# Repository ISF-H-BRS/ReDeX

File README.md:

# ReDeX: Water Purification Measurements

## Introduction

This repository contains a public archive of electronics, firmware and software developed as part of the project [ReDeX](https://www.h-brs.de/de/entwicklung-einer-reduktiven-behandlungsmethode-zur-entfernung-von-desinfektionsnebenprodukten-und) that was conducted at Bonn-Rhein-Sieg University of Applied Sciences from 2019 to 2022.

The goal of this sub-project was to develop a sensor network allowing various parameters inside a water purification system to be monitored and analyzed in order to gain a better understanding of the chemical and physical processes involved.

The system is composed of sensor nodes which can be used either as standalone devices connected to a PC over USB or as a sensor network accessed over TCP/IP via a central hub. Every sensor provides complete galvanic isolation in order to prevent any possibility of cross-currents which could potentially invalidate measurements.

The parameters that can be measured include conductance, pH/ORP levels and temperature. In addition a potentiostat for cyclic voltammetry was developed, providing a compliance voltage of ±4 V and a dynamic range of approx. 1 pA to 10 mA.

Every sensor node has a corresponding user software providing a GUI for individual measurements. The complete sensor network can be accessed via the central hub by means of a shared library with optional LabVIEW integration.

## License

All source code for the software and firmware components (including the LabVIEW code) is licensed under the terms of the GNU General Public License (GPL). All schematics and CAD files for EAGLE and FreeCAD are licensed under the terms of the Creative Commons Attribution-ShareAlike International Public License (CC BY-SA). See COPYING in the respective subdirectories for details.

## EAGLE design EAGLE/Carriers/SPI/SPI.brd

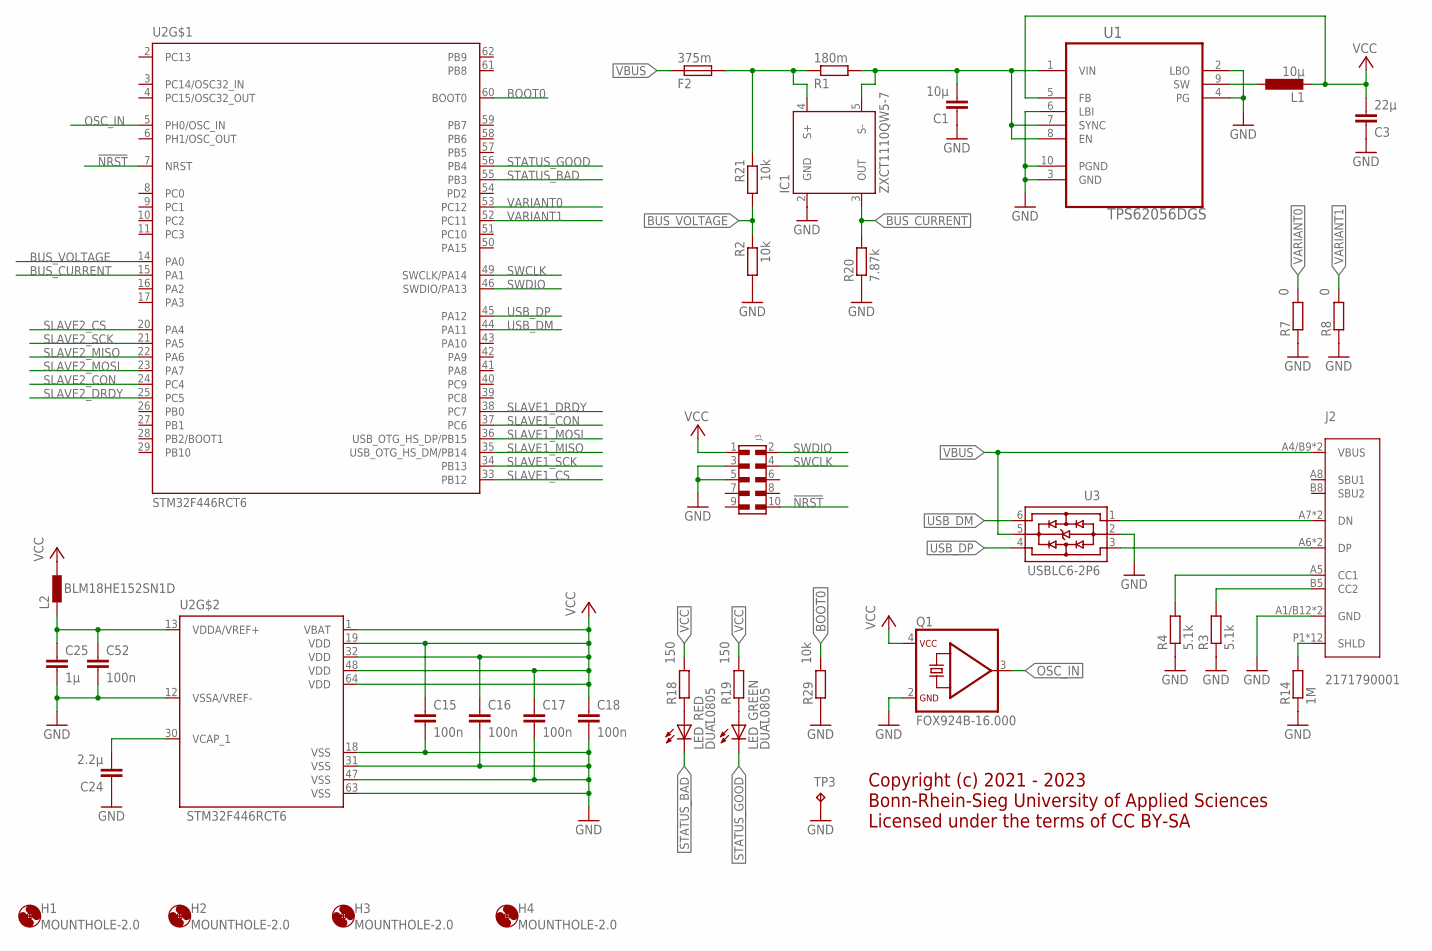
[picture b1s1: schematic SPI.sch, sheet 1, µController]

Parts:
C1: 10µ; C0603
C3: 22µ; C0603
C15, C16, C17, C18, C52: 100n; C0603
C24: 2.2µ; C0603
C25: 1µ; C0603
F2: 375m; R0603
H1, H2, H3, H4: MOUNTHOLE-2.0; 2.0
IC1: ZXCT1110QW5-7; SOT23-5L
J2: 2171790001; 2171790001_MOL
J3: 6210XX21021_62101021021; 62101021021
L1: 10µ; 2SMD
L2: BLM18HE152SN1D; 0603
LED_: DUAL0805; CHIPLEDX2
Q1: FOX924B-16.000; FOX924B
R1: 180m; R0603
R2, R21, R29: 10k; R0603
R3, R4: 5.1k; R0603
R7, R8: 0; R0603
R14: 1M; R0603
R18, R19: 150; R0603
R20: 7.87k; R0603
TP3: TP3.8X2.03; 3.8X2.03
U1: TPS62056DGS; SOP50P490X110-10N
U2: STM32F446RCT6; LQFP64
U3: USBLC6-2P6; SOT-666

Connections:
!NRST: J3.10, U2.7 (NRST)
BOOT0: R29.2, U2.60 (BOOT0)
BUS_CURRENT: IC1.3 (OUT), R20.2, U2.15 (PA1)
BUS_VOLTAGE: R2.1, R21.2, U2.14 (PA0)
GND: C1.1, C3.1, C15.2, C16.2, C17.2, C18.2, C24.1, C25.2, C52.2, IC1.2 (GND), J2.A1/B12 (GND), J2.B1/A12 (GND), J3.3, J3.5, Q1.2 (GND), R2.2, R3.1, R4.1, R7.1, R8.1, R14.1, R20.1, R29.1, TP3.TP, U1.2 (LBO), U1.3 (GND), U1.4 (PG), U1.6 (LBI), U1.10 (PGND), U2.12 (VSSA/VREF-), U2.18 (VSS), U2.31 (VSS), U2.47 (VSS), U2.63 (VSS), U3.2; also elsewhere on the board
unnamed: J2.P1 (SHLD), J2.P2 (SHLD), J2.P3 (SHLD), J2.P4 (SHLD), J2.S1 (SHLD), J2.S2 (SHLD), J2.S3 (SHLD), J2.S4 (SHLD), J2.S5 (SHLD), J2.S6 (SHLD), J2.S7 (SHLD), J2.S8 (SHLD), R14.2
unnamed: C1.2, IC1.5 (S-), R1.2, U1.1 (VIN), U1.7 (SYNC), U1.8 (EN)
unnamed: L1.P$1 (1), U1.9 (SW)
unnamed: J2.A6 (DP), J2.B6 (DP), U3.3
unnamed: J2.A7 (DN), J2.B7 (DN), U3.1
unnamed: J2.B5 (CC2), R3.2
unnamed: J2.A5 (CC1), R4.2
unnamed: C25.1, C52.1, L2.2, U2.13 (VDDA/VREF+)
unnamed: F2.2, IC1.4 (S+), R1.1, R21.1
unnamed: C24.2, U2.30 (VCAP_1)
unnamed: LED_.A1 (A), R18.1
unnamed: LED_.A2 (A), R19.1
OSC_IN: Q1.3 (OUT), U2.5 (PH0/OSC_IN)
SLAVE1_CON: U2.37 (PC6); also elsewhere on the board
SLAVE1_CS: U2.33 (PB12); also elsewhere on the board
SLAVE1_DRDY: U2.38 (PC7); also elsewhere on the board
SLAVE1_MISO: U2.35 (USB_OTG_HS_DM/PB14); also elsewhere on the board
SLAVE1_MOSI: U2.36 (USB_OTG_HS_DP/PB15); also elsewhere on the board
SLAVE1_SCK: U2.34 (PB13); also elsewhere on the board
SLAVE2_CON: U2.24 (PC4); also elsewhere on the board
SLAVE2_CS: U2.20 (PA4); also elsewhere on the board
SLAVE2_DRDY: U2.25 (PC5); also elsewhere on the board
SLAVE2_MISO: U2.22 (PA6); also elsewhere on the board
SLAVE2_MOSI: U2.23 (PA7); also elsewhere on the board
SLAVE2_SCK: U2.21 (PA5); also elsewhere on the board
STATUS_BAD: LED_.C1 (C), U2.55 (PB3)
STATUS_GOOD: LED_.C2 (C), U2.56 (PB4)
SWCLK: J3.4, U2.49 (SWCLK/PA14)
SWDIO: J3.2, U2.46 (SWDIO/PA13)
USB_DM: U2.44 (PA11), U3.6
USB_DP: U2.45 (PA12), U3.4
VARIANT0: R7.2, U2.53 (PC12)
VARIANT1: R8.2, U2.52 (PC11)
VBUS: F2.1, J2.A4/B9 (VBUS), J2.B4/A9 (VBUS), U3.5
VCC: C3.2, C15.1, C16.1, C17.1, C18.1, J3.1, L1.P$2 (2), L2.1, Q1.4 (VCC), R18.2, R19.2, U1.5 (FB), U2.1 (VBAT), U2.19 (VDD), U2.32 (VDD), U2.48 (VDD), U2.64 (VDD); also elsewhere on the board

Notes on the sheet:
Copyright (c) 2021 - 2023 Bonn-Rhein-Sieg University of Applied Sciences Licensed under the terms of CC BY-SA

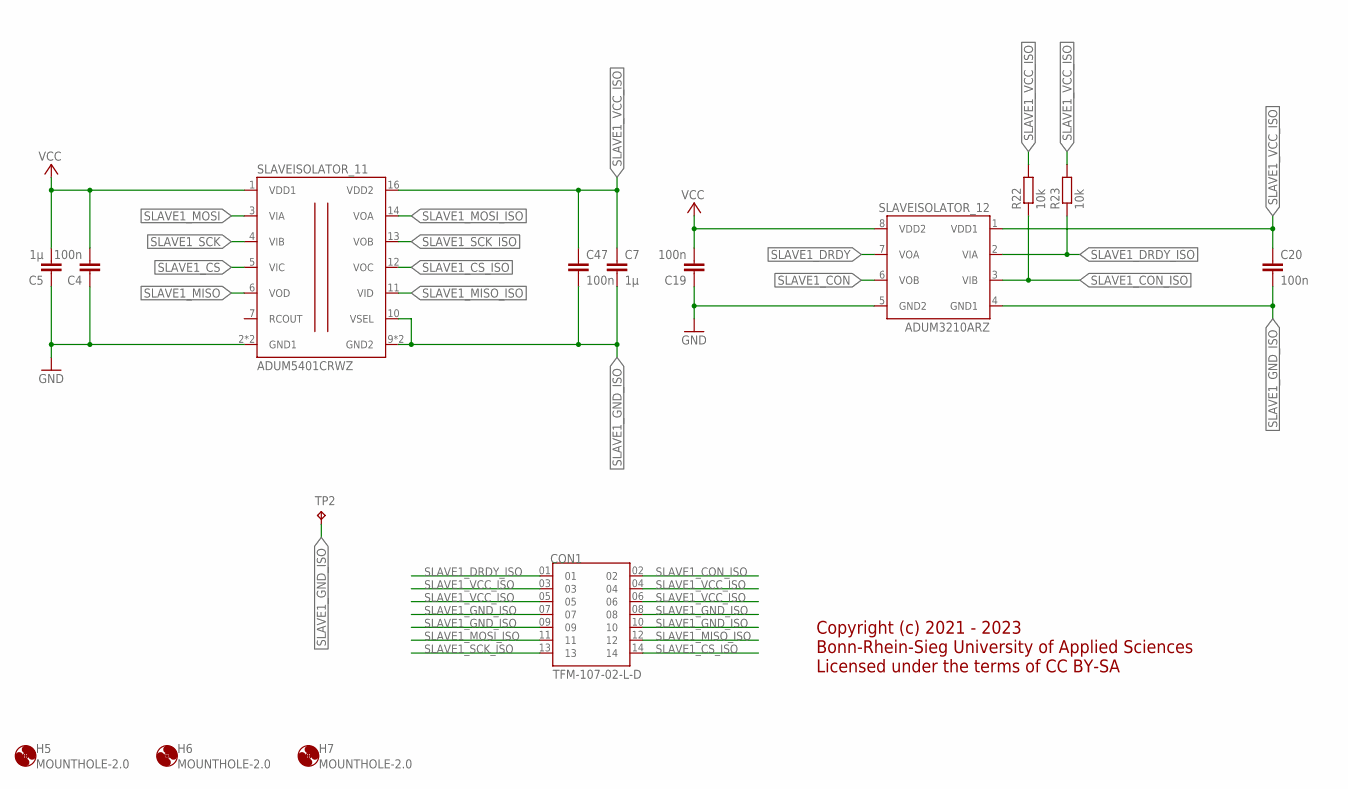
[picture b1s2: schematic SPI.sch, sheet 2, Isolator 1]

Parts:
C4, C19, C20, C47: 100n; C0603
C5, C7: 1µ; C0603
CON1: TFM-107-02-L-D; SAMTEC_TFM-107-02-L-D
H5, H6, H7: MOUNTHOLE-2.0; 2.0
R22, R23: 10k; R0603
SLAVEISOLATOR_11: ADUM5401CRWZ; SO16W
SLAVEISOLATOR_12: ADUM3210ARZ; SOIC8
TP2: TP3.8X2.03; 3.8X2.03

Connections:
GND: C4.1, C5.1, C19.1, SLAVEISOLATOR_11.2 (GND1), SLAVEISOLATOR_11.8 (GND1), SLAVEISOLATOR_12.5 (GND2); also elsewhere on the board
SLAVE1_CON: SLAVEISOLATOR_12.6 (VOB); also elsewhere on the board
SLAVE1_CON_ISO: CON1.02, R22.1, SLAVEISOLATOR_12.3 (VIB)
SLAVE1_CS: SLAVEISOLATOR_11.5 (VIC); also elsewhere on the board
SLAVE1_CS_ISO: CON1.14, SLAVEISOLATOR_11.12 (VOC)
SLAVE1_DRDY: SLAVEISOLATOR_12.7 (VOA); also elsewhere on the board
SLAVE1_DRDY_ISO: CON1.01, R23.1, SLAVEISOLATOR_12.2 (VIA)
SLAVE1_GND_ISO: C7.2, C20.2, C47.2, CON1.07, CON1.08, CON1.09, CON1.10, SLAVEISOLATOR_11.9 (GND2), SLAVEISOLATOR_11.10 (VSEL), SLAVEISOLATOR_11.15 (GND2), SLAVEISOLATOR_12.4 (GND1), TP2.TP
SLAVE1_MISO: SLAVEISOLATOR_11.6 (VOD); also elsewhere on the board
SLAVE1_MISO_ISO: CON1.12, SLAVEISOLATOR_11.11 (VID)
SLAVE1_MOSI: SLAVEISOLATOR_11.3 (VIA); also elsewhere on the board
SLAVE1_MOSI_ISO: CON1.11, SLAVEISOLATOR_11.14 (VOA)
SLAVE1_SCK: SLAVEISOLATOR_11.4 (VIB); also elsewhere on the board
SLAVE1_SCK_ISO: CON1.13, SLAVEISOLATOR_11.13 (VOB)
SLAVE1_VCC_ISO: C7.1, C20.1, C47.1, CON1.03, CON1.04, CON1.05, CON1.06, R22.2, R23.2, SLAVEISOLATOR_11.16 (VDD2), SLAVEISOLATOR_12.1 (VDD1)
VCC: C4.2, C5.2, C19.2, SLAVEISOLATOR_11.1 (VDD1), SLAVEISOLATOR_12.8 (VDD2); also elsewhere on the board

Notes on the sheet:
Copyright (c) 2021 - 2023 Bonn-Rhein-Sieg University of Applied Sciences Licensed under the terms of CC BY-SA

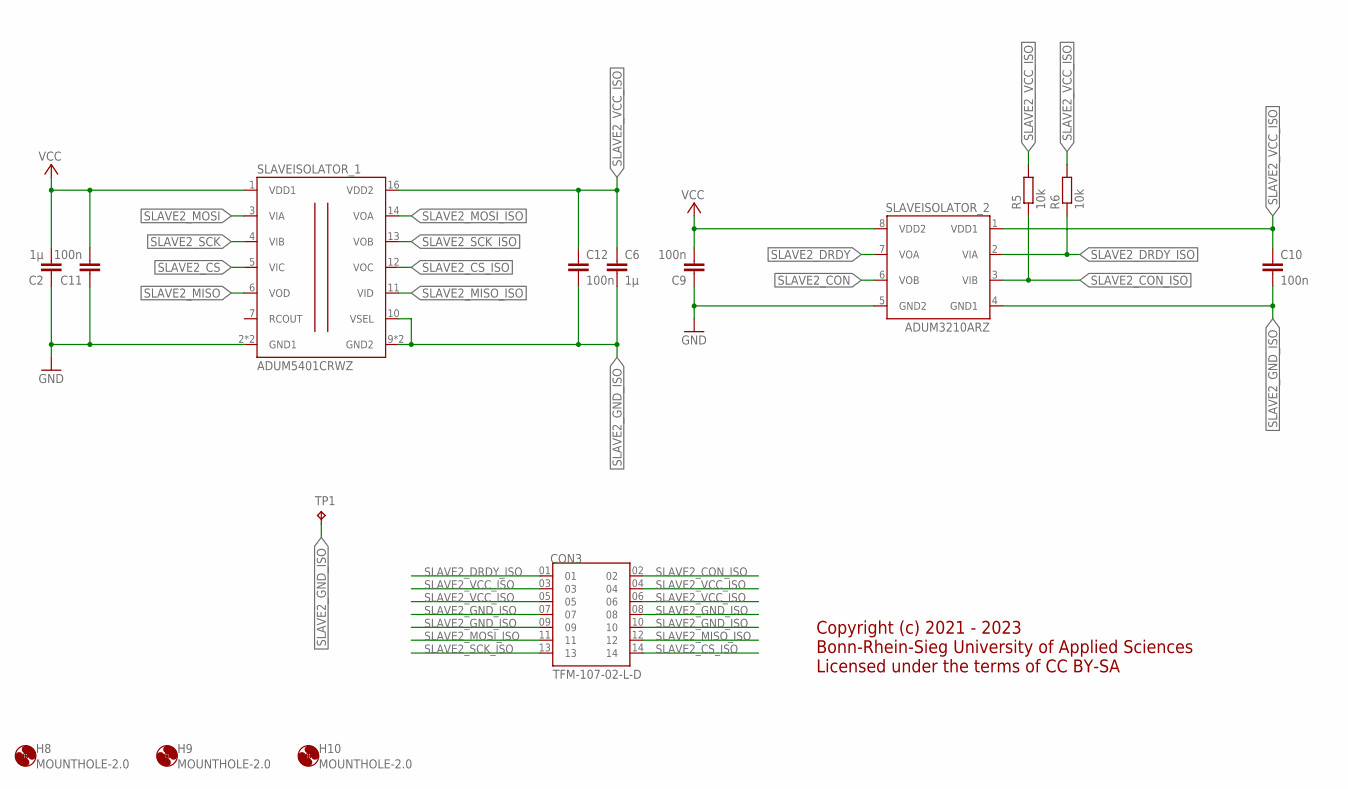
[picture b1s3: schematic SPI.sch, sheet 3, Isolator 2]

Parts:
C2, C6: 1µ; C0603
C9, C10, C11, C12: 100n; C0603
CON3: TFM-107-02-L-D; SAMTEC_TFM-107-02-L-D
H8, H9, H10: MOUNTHOLE-2.0; 2.0
R5, R6: 10k; R0603
SLAVEISOLATOR_1: ADUM5401CRWZ; SO16W
SLAVEISOLATOR_2: ADUM3210ARZ; SOIC8
TP1: TP3.8X2.03; 3.8X2.03

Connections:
GND: C2.1, C9.1, C11.1, SLAVEISOLATOR_1.2 (GND1), SLAVEISOLATOR_1.8 (GND1), SLAVEISOLATOR_2.5 (GND2); also elsewhere on the board
SLAVE2_CON: SLAVEISOLATOR_2.6 (VOB); also elsewhere on the board
SLAVE2_CON_ISO: CON3.02, R5.1, SLAVEISOLATOR_2.3 (VIB)
SLAVE2_CS: SLAVEISOLATOR_1.5 (VIC); also elsewhere on the board
SLAVE2_CS_ISO: CON3.14, SLAVEISOLATOR_1.12 (VOC)
SLAVE2_DRDY: SLAVEISOLATOR_2.7 (VOA); also elsewhere on the board
SLAVE2_DRDY_ISO: CON3.01, R6.1, SLAVEISOLATOR_2.2 (VIA)
SLAVE2_GND_ISO: C6.2, C10.2, C12.2, CON3.07, CON3.08, CON3.09, CON3.10, SLAVEISOLATOR_1.9 (GND2), SLAVEISOLATOR_1.10 (VSEL), SLAVEISOLATOR_1.15 (GND2), SLAVEISOLATOR_2.4 (GND1), TP1.TP
SLAVE2_MISO: SLAVEISOLATOR_1.6 (VOD); also elsewhere on the board
SLAVE2_MISO_ISO: CON3.12, SLAVEISOLATOR_1.11 (VID)
SLAVE2_MOSI: SLAVEISOLATOR_1.3 (VIA); also elsewhere on the board
SLAVE2_MOSI_ISO: CON3.11, SLAVEISOLATOR_1.14 (VOA)
SLAVE2_SCK: SLAVEISOLATOR_1.4 (VIB); also elsewhere on the board
SLAVE2_SCK_ISO: CON3.13, SLAVEISOLATOR_1.13 (VOB)
SLAVE2_VCC_ISO: C6.1, C10.1, C12.1, CON3.03, CON3.04, CON3.05, CON3.06, R5.2, R6.2, SLAVEISOLATOR_1.16 (VDD2), SLAVEISOLATOR_2.1 (VDD1)
VCC: C2.2, C9.2, C11.2, SLAVEISOLATOR_1.1 (VDD1), SLAVEISOLATOR_2.8 (VDD2); also elsewhere on the board

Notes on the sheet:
Copyright (c) 2021 - 2023 Bonn-Rhein-Sieg University of Applied Sciences Licensed under the terms of CC BY-SA

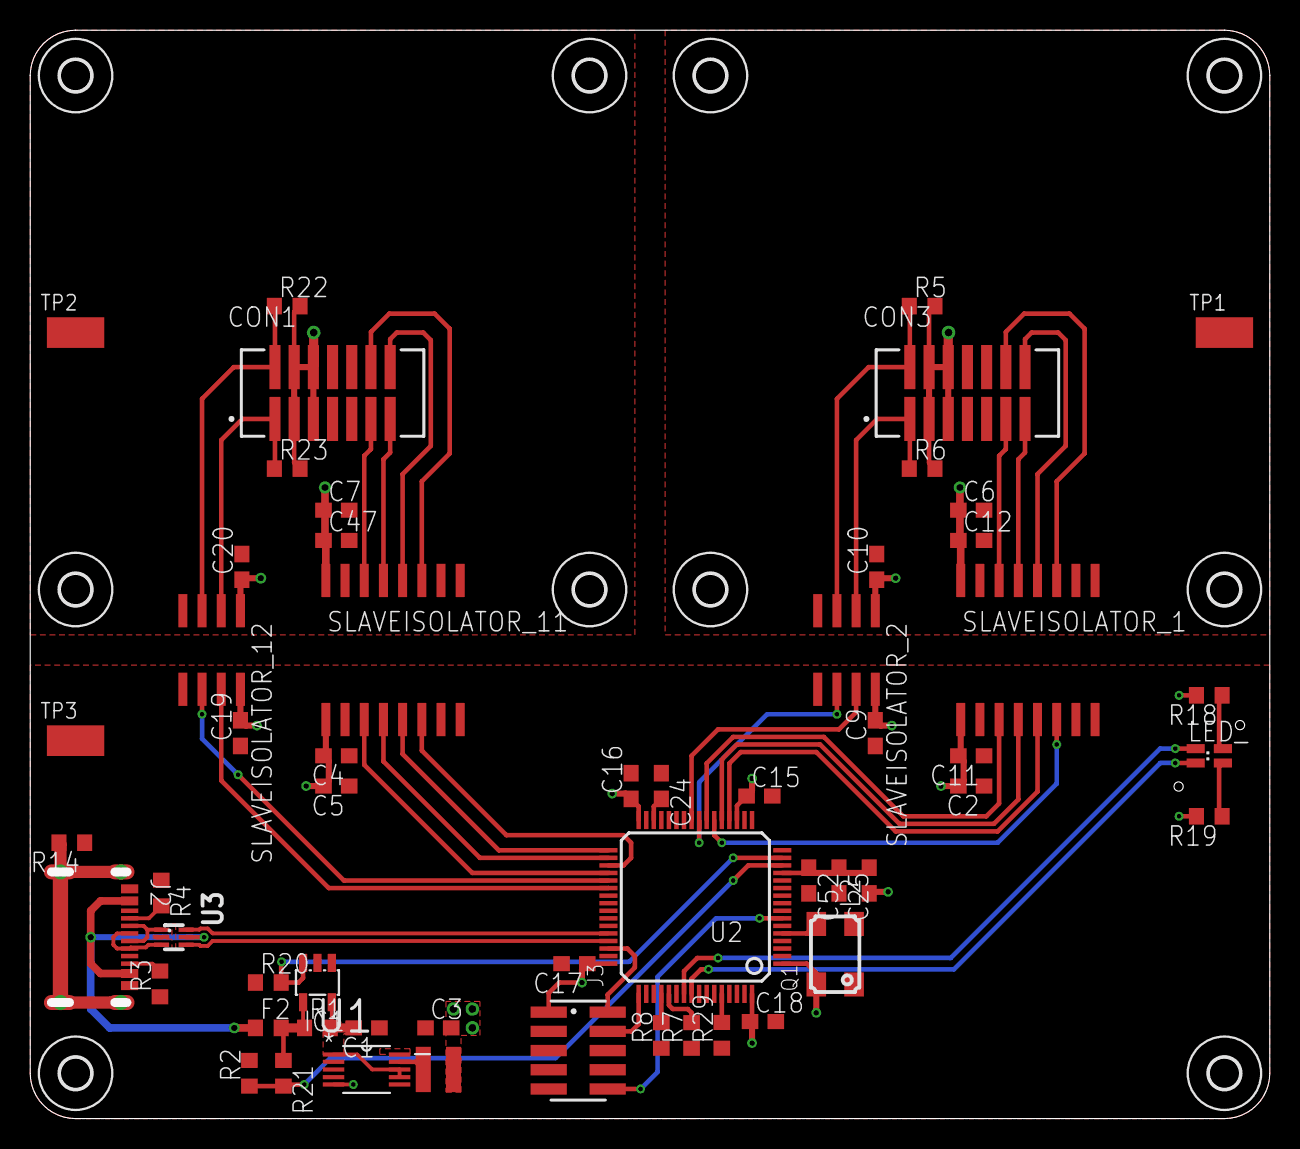
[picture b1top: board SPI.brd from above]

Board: 2 copper layers, 81.4 x 71.4 mm, 67 parts (0 on the bottom side), 56 nets.

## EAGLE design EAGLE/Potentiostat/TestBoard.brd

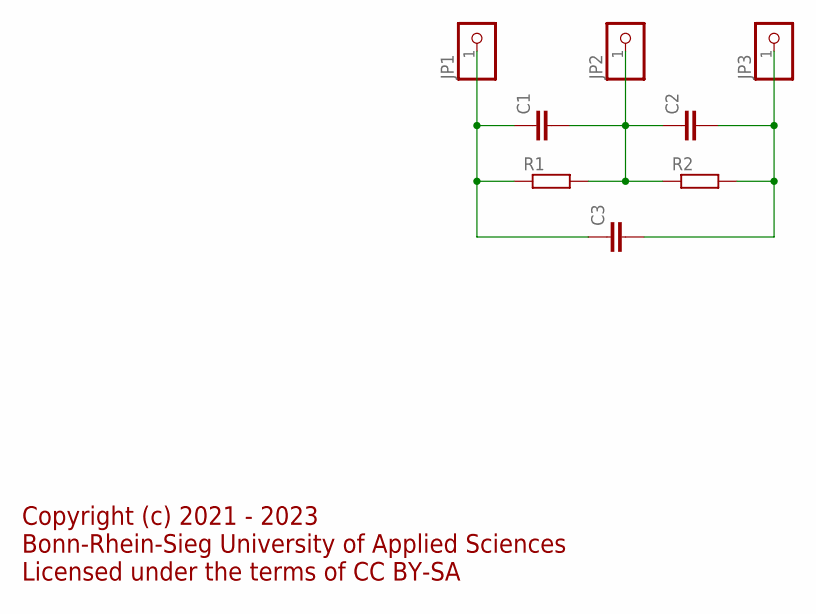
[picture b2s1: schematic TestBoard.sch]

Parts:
C1, C2, C3: C-EUC0603; C0603
JP1, JP2, JP3: PINHD-1X1; 1X01
R1, R2: R-EU_R0603; R0603

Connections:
unnamed: C1.1, C3.1, JP1.1, R1.1
unnamed: C1.2, C2.1, JP2.1, R1.2, R2.1
unnamed: C2.2, C3.2, JP3.1, R2.2

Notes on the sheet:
Copyright (c) 2021 - 2023 Bonn-Rhein-Sieg University of Applied Sciences Licensed under the terms of CC BY-SA

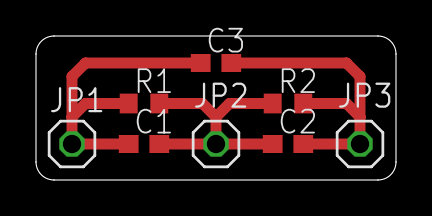
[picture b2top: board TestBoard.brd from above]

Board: 2 copper layers, 20.0 x 8.0 mm, 8 parts (0 on the bottom side), 3 nets.

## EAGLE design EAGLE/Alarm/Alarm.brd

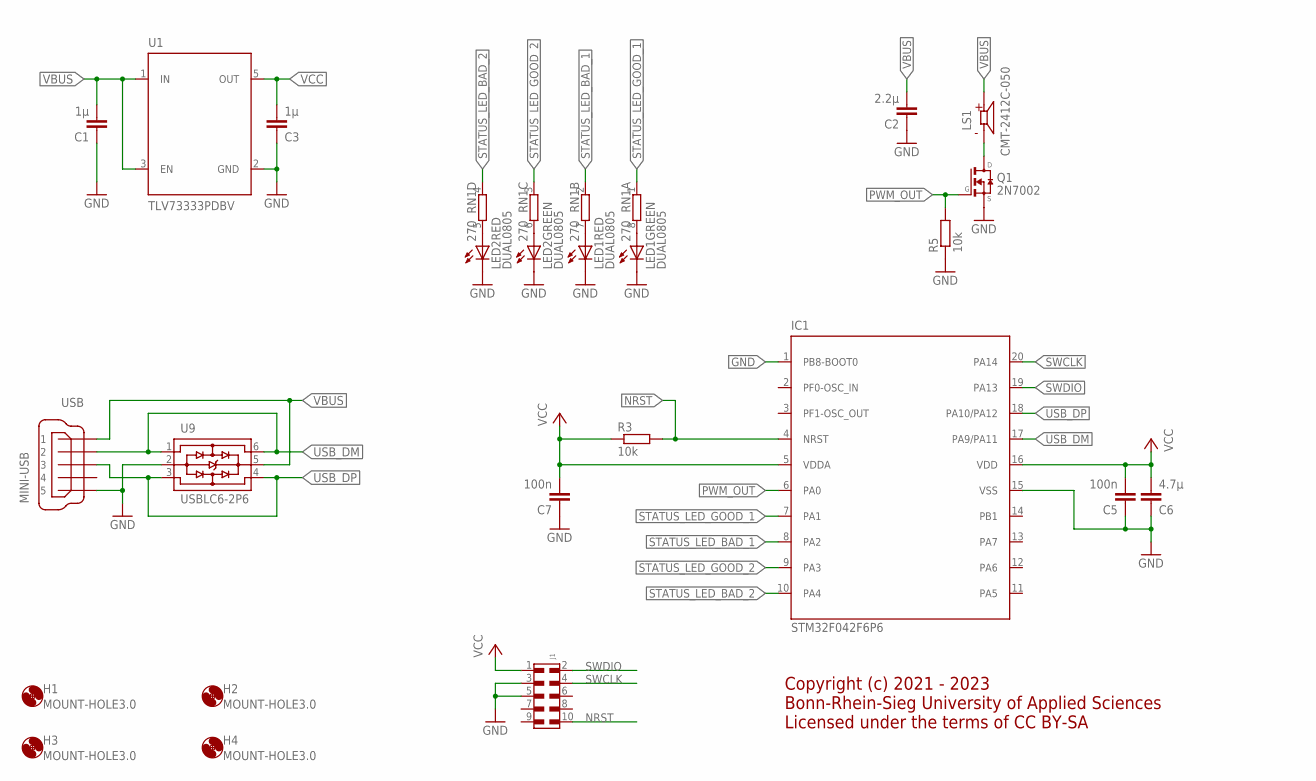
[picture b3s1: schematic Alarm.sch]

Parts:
C1, C3: 1µ; C0603
C2: 2.2µ; C0603
C5, C7: 100n; C0603
C6: 4.7µ; C0603
H1, H2, H3, H4: MOUNT-HOLE3.0; 3,0
IC1: STM32F042F6P6; TSSOP20
J1: 6210XX21021_62101021021; 62101021021
LED1, LED2: DUAL0805; CHIPLEDX2
LS1: CMT-2412C-050; CUI_CMT-2412C-050
Q1: 2N7002; SOT23
R3, R5: 10k; R0603
RN1: 270; EXB38V
U1: TLV73333PDBV; SOT-23
U9: USBLC6-2P6; SOT-666; PARTNO *
USB: MINI-USB; 32005-201

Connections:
GND: C1.1, C2.1, C3.1, C5.1, C6.1, C7.1, IC1.1 (PB8-BOOT0), IC1.15 (VSS), J1.3, J1.5, LED1.C1 (C), LED1.C2 (C), LED2.C1 (C), LED2.C2 (C), Q1.2 (S), R5.1, U1.2 (GND), U9.2, USB.5
unnamed: LED2.A1 (A), RN1.5 (2)
unnamed: LED2.A2 (A), RN1.6 (2)
unnamed: LED1.A1 (A), RN1.7 (2)
unnamed: LED1.A2 (A), RN1.8 (2)
unnamed: LS1.N, Q1.3 (D)
NRST: IC1.4 (NRST), J1.10, R3.2
PWM_OUT: IC1.6 (PA0), Q1.1 (G), R5.2
STATUS_LED_BAD_1: IC1.8 (PA2), RN1.2 (1)
STATUS_LED_BAD_2: IC1.10 (PA4), RN1.4 (1)
STATUS_LED_GOOD_1: IC1.7 (PA1), RN1.1
STATUS_LED_GOOD_2: IC1.9 (PA3), RN1.3 (1)
SWCLK: IC1.20 (PA14), J1.4
SWDIO: IC1.19 (PA13), J1.2
USB_DM: IC1.17 (PA9/PA11), U9.1, U9.6, USB.2
USB_DP: IC1.18 (PA10/PA12), U9.3, U9.4, USB.3
VBUS: C1.2, C2.2, LS1.P, U1.1 (IN), U1.3 (EN), U9.5, USB.1
VCC: C3.2, C5.2, C6.2, C7.2, IC1.5 (VDDA), IC1.16 (VDD), J1.1, R3.1, U1.5 (OUT)

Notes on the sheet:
Copyright (c) 2021 - 2023 Bonn-Rhein-Sieg University of Applied Sciences Licensed under the terms of CC BY-SA

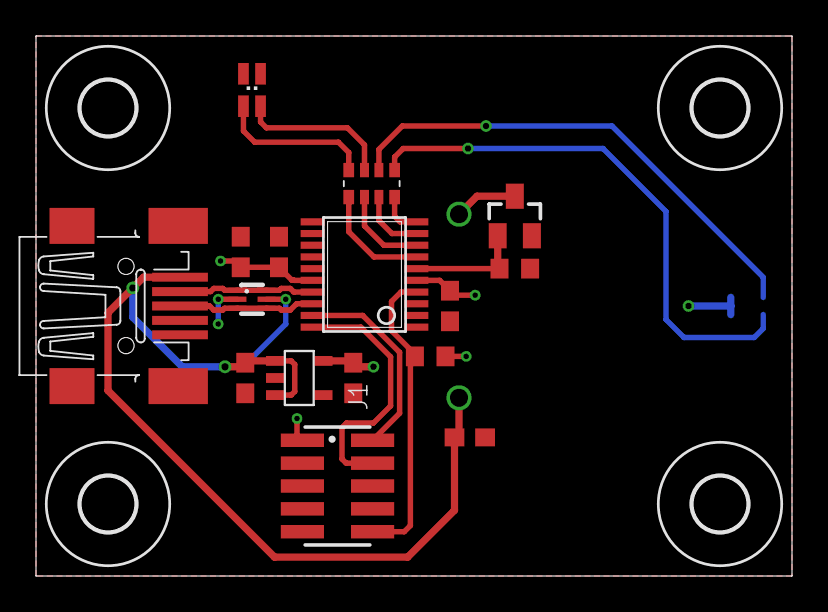
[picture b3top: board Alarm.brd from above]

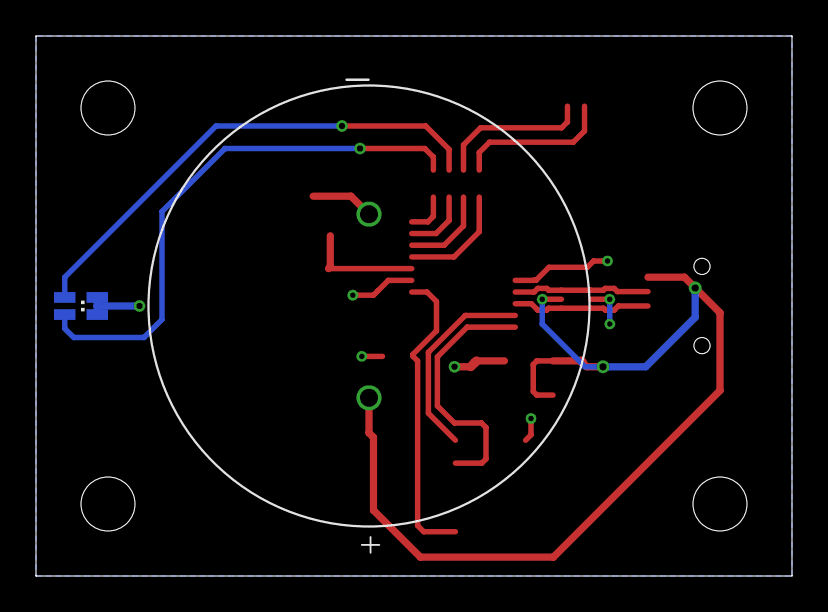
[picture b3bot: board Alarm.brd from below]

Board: 2 copper layers, 42.0 x 30.0 mm, 22 parts (2 on the bottom side), 18 nets.

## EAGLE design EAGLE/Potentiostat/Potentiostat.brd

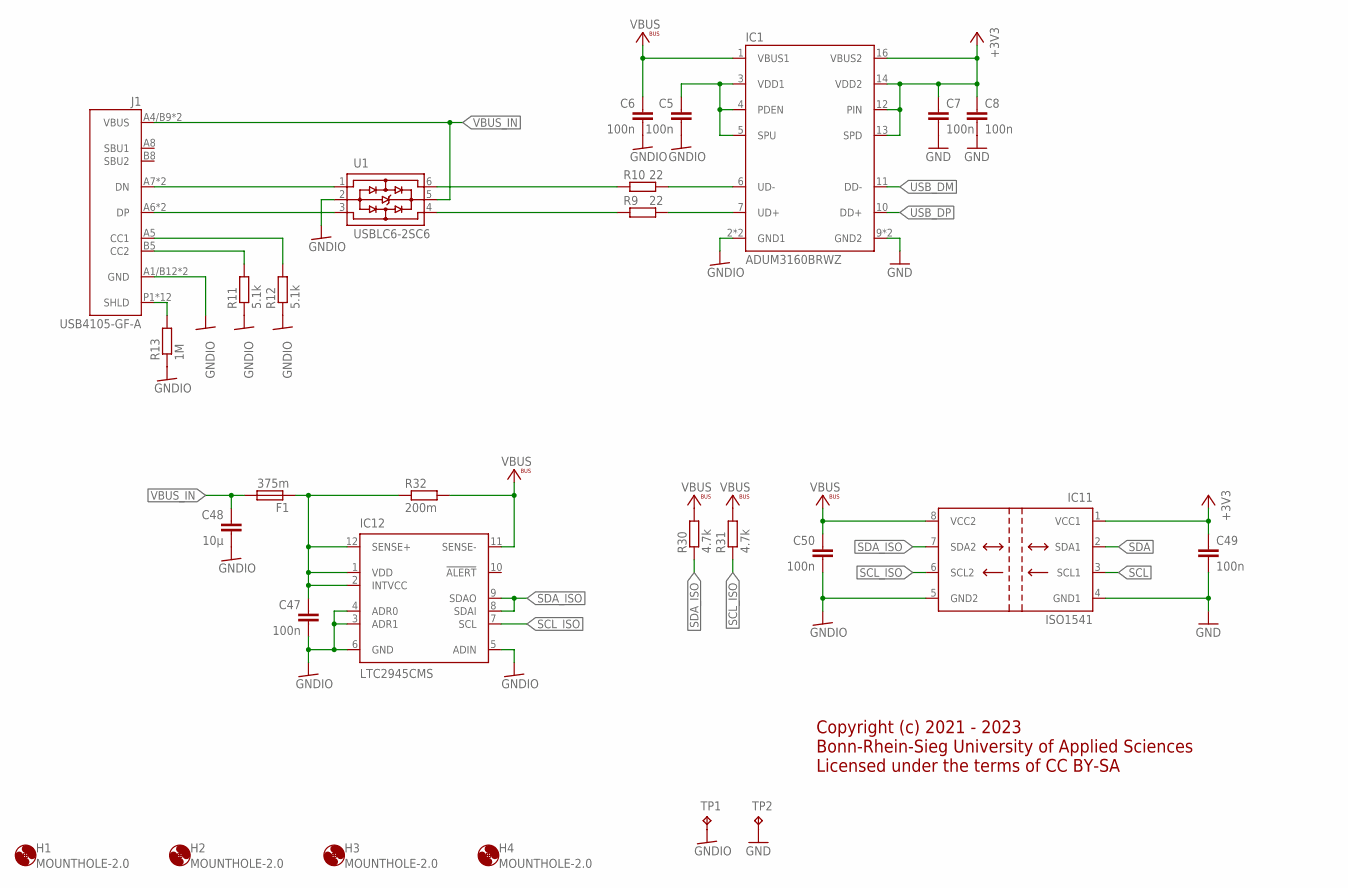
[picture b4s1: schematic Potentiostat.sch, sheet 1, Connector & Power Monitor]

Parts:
C5, C6, C7, C8, C47, C49, C50: 100n; C0603
C48: 10µ; C0603
F1: 375m; R0603
H1, H2, H3, H4: MOUNTHOLE-2.0; 2.0
IC1: ADUM3160BRWZ; SO16W
IC11: ISO1541; SOIC8
IC12: LTC2945CMS; MSOP12
J1: USB4105-GF-A
R9, R10: 22; R0603
R11, R12: 5.1k; R0603
R13: 1M; R0603
R30, R31: 4.7k; R0603
R32: 200m; R0805
TP1, TP2: TP3.8X2.03; 3.8X2.03
U1: USBLC6-2SC6; SOT23-6L

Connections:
+3V3: C7.1, C8.1, C49.1, IC1.12 (PIN), IC1.13 (SPD), IC1.14 (VDD2), IC1.16 (VBUS2), IC11.1 (VCC1); also elsewhere on the board
GND: C7.2, C8.2, C49.2, IC1.9 (GND2), IC1.15 (GND2), IC11.4 (GND1), TP2.TP; also elsewhere on the board
GNDIO: C5.2, C6.2, C47.2, C48.2, C50.2, IC1.2 (GND1), IC1.8 (GND1), IC11.5 (GND2), IC12.3 (ADR1), IC12.4 (ADR0), IC12.5 (ADIN), IC12.6 (GND), J1.A1/B12 (GND), J1.B1/A12 (GND), R11.1, R12.1, R13.1, TP1.TP, U1.2; also elsewhere on the board
unnamed: C5.1, IC1.3 (VDD1), IC1.4 (PDEN), IC1.5 (SPU)
unnamed: R10.1, U1.6
unnamed: R9.1, U1.4
unnamed: IC1.7 (UD+), R9.2
unnamed: C47.1, F1.1, IC12.1 (VDD), IC12.2 (INTVCC), IC12.12 (SENSE+), R32.1
unnamed: J1.A7 (DN), J1.B7 (DN), U1.1
unnamed: J1.A6 (DP), J1.B6 (DP), U1.3
unnamed: J1.A5 (CC1), R12.2
unnamed: J1.B5 (CC2), R11.2
unnamed: J1.P1 (SHLD), J1.P2 (SHLD), J1.P3 (SHLD), J1.P4 (SHLD), J1.S1 (SHLD), J1.S2 (SHLD), J1.S3 (SHLD), J1.S4 (SHLD), J1.S5 (SHLD), J1.S6 (SHLD), J1.S7 (SHLD), J1.S8 (SHLD), R13.2
unnamed: IC1.6 (UD-), R10.2
SCL: IC11.3 (SCL1); also elsewhere on the board
SCL_ISO: IC11.6 (SCL2), IC12.7 (SCL), R31.1
SDA: IC11.2 (SDA1); also elsewhere on the board
SDA_ISO: IC11.7 (SDA2), IC12.8 (SDAI), IC12.9 (SDAO), R30.1
USB_DM: IC1.11 (DD-); also elsewhere on the board
USB_DP: IC1.10 (DD+); also elsewhere on the board
VBUS: C6.1, C50.1, IC1.1 (VBUS1), IC11.8 (VCC2), IC12.11 (SENSE-), R30.2, R31.2, R32.2; also elsewhere on the board
VBUS_IN: C48.1, F1.2, J1.A4/B9 (VBUS), J1.B4/A9 (VBUS), U1.5

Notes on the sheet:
Copyright (c) 2021 - 2023 Bonn-Rhein-Sieg University of Applied Sciences Licensed under the terms of CC BY-SA

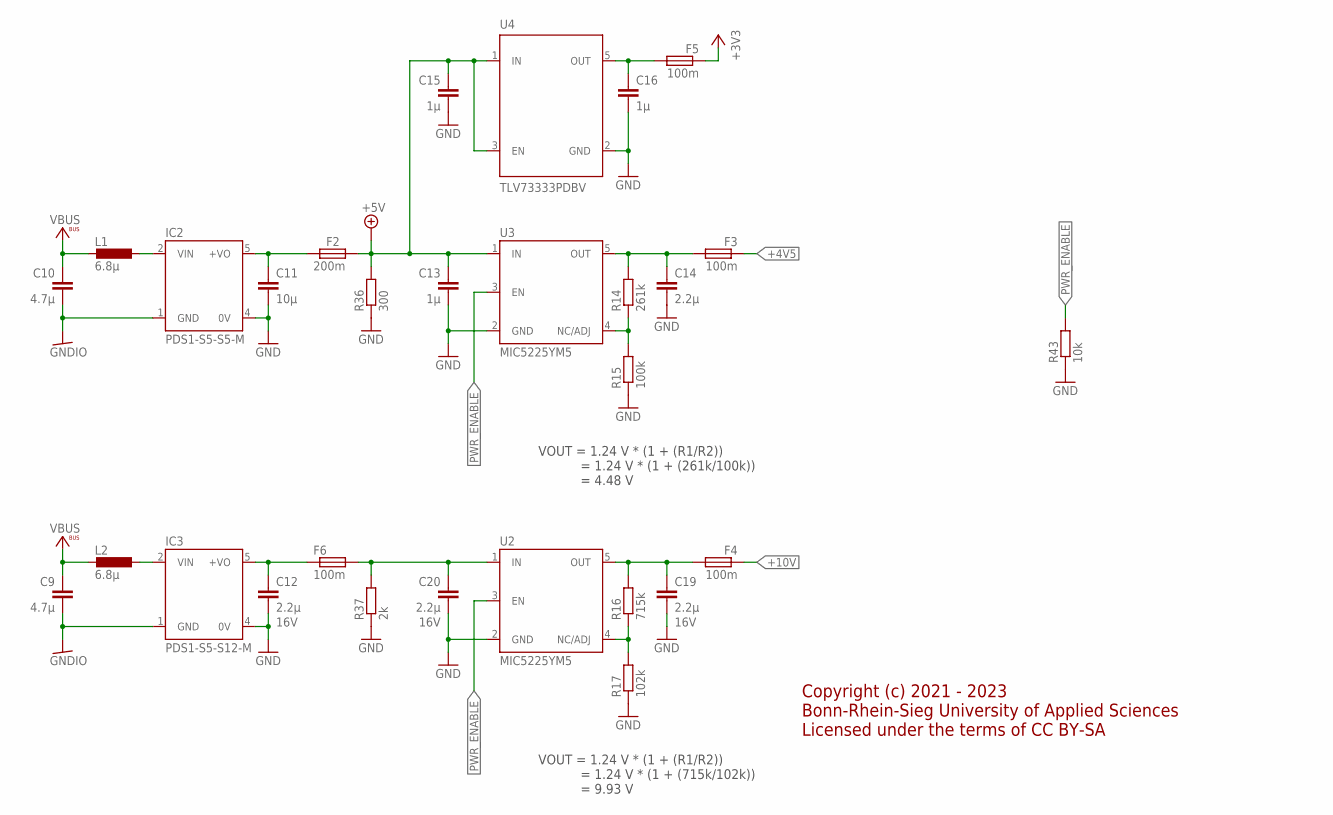
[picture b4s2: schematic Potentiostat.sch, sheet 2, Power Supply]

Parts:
C9, C10: 4.7µ; C0603
C11: 10µ; C0603
C12, C19, C20: 2.2µ; C0603; RATING 16V
C13, C15, C16: 1µ; C0603
C14: 2.2µ; C0603
F2: 200m; R0603
F3, F4, F5, F6: 100m; R0603
IC2: PDS1-S5-S5-M; PDS1-M
IC3: PDS1-S5-S12-M; PDS1-M
L1, L2: 6.8µ; L0603
R14: 261k; R0603
R15: 100k; R0603
R16: 715k; R0603
R17: 102k; R0603
R36: 300; R0805
R37: 2k; R0805
R43: 10k; R0603
U2, U3: MIC5225YM5; SOT23-5L
U4: TLV73333PDBV; SOT-23

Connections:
+3V3: F5.1; also elsewhere on the board
+4V5: F3.1; also elsewhere on the board
+5V: C13.1, C15.1, F2.2, R36.2, U3.1 (IN), U4.1 (IN), U4.3 (EN)
+10V: F4.1; also elsewhere on the board
GND: C11.2, C12.2, C13.2, C14.2, C15.2, C16.2, C19.2, C20.2, IC2.4 (0V), IC3.4 (0V), R15.1, R17.1, R36.1, R37.1, R43.1, U2.2 (GND), U3.2 (GND), U4.2 (GND); also elsewhere on the board
GNDIO: C9.2, C10.2, IC2.1 (GND), IC3.1 (GND); also elsewhere on the board
unnamed: R14.1, R15.2, U3.4 (NC/ADJ)
unnamed: C20.1, F6.2, R37.2, U2.1 (IN)
unnamed: R16.1, R17.2, U2.4 (NC/ADJ)
unnamed: C12.1, F6.1, IC3.5 (+VO)
unnamed: C16.1, F5.2, U4.5 (OUT)
unnamed: C14.1, F3.2, R14.2, U3.5 (OUT)
unnamed: C19.1, F4.2, R16.2, U2.5 (OUT)
unnamed: IC2.2 (VIN), L1.1
unnamed: IC3.2 (VIN), L2.1
unnamed: C11.1, F2.1, IC2.5 (+VO)
PWR_ENABLE: R43.2, U2.3 (EN), U3.3 (EN); also elsewhere on the board
VBUS: C9.1, C10.1, L1.2, L2.2; also elsewhere on the board

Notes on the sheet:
VOUT = 1.24 V * (1 + (R1/R2)) = 1.24 V * (1 + (261k/100k)) = 4.48 V
VOUT = 1.24 V * (1 + (R1/R2)) = 1.24 V * (1 + (715k/102k)) = 9.93 V
Copyright (c) 2021 - 2023 Bonn-Rhein-Sieg University of Applied Sciences Licensed under the terms of CC BY-SA

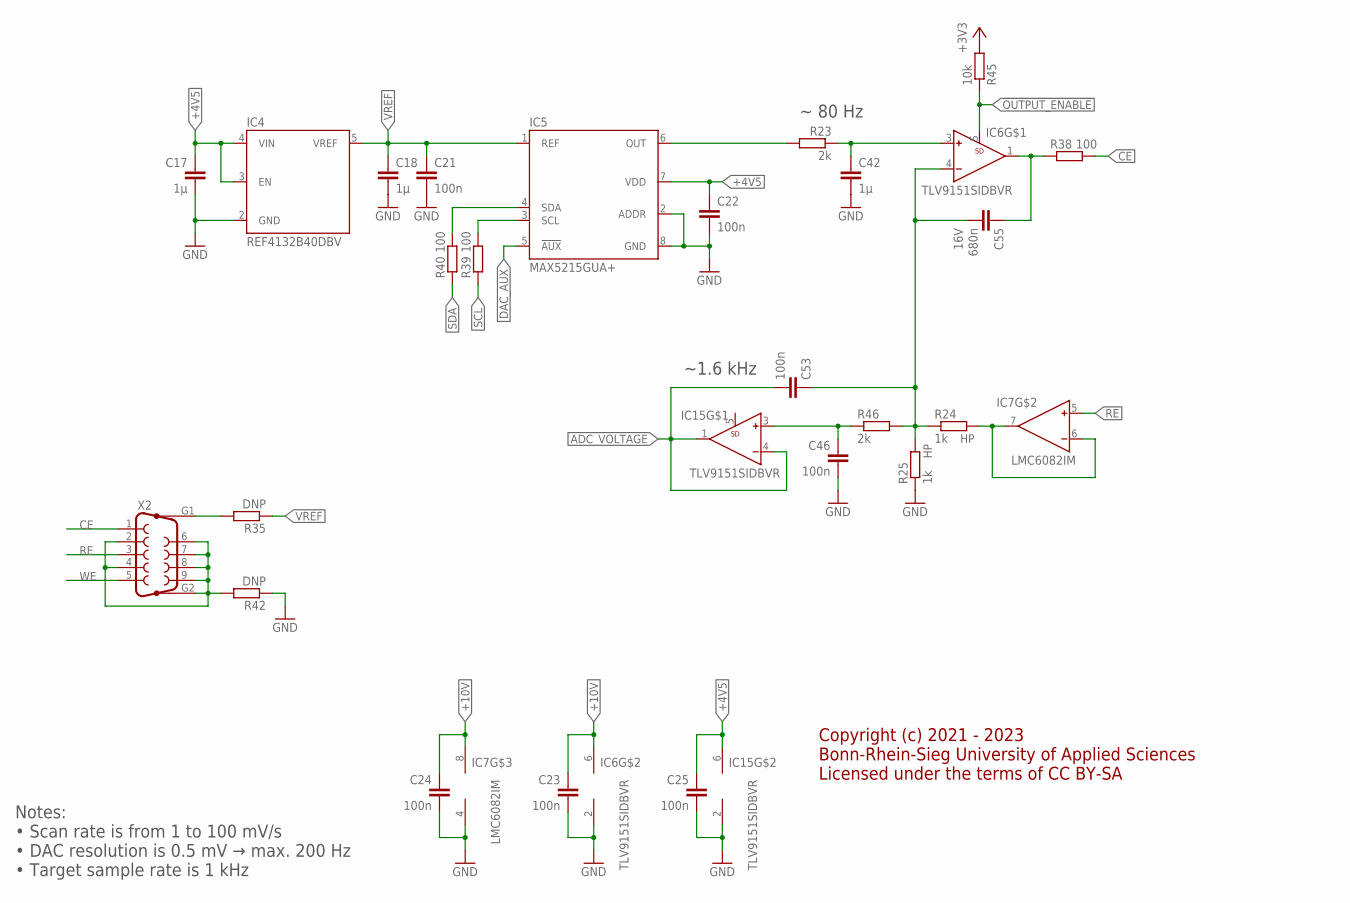
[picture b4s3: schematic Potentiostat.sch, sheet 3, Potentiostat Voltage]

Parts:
C17, C18, C42: 1µ; C0603
C21, C22, C23, C24, C25, C46, C53: 100n; C0603
C55: 680n; C0603; RATING 16V
IC4: REF4132B40DBV; SOT23-5
IC5: MAX5215GUA+; MSOP8
IC6, IC15: TLV9151SIDBVR; SOT23-6
IC7: LMC6082IM; SOIC8
R23, R46: 2k; R0603
R24, R25: 1k; R0603
R35, R42: DNP; R0603
R38, R39, R40: 100; R0603
R45: 10k; R0603
X2: A-DF_09

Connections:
!OUTPUT_ENABLE: IC6.5 (SD), R45.1; also elsewhere on the board
+3V3: R45.2; also elsewhere on the board
+4V5: C17.1, C22.1, C25.1, IC4.3 (EN), IC4.4 (VIN), IC5.7 (VDD), IC15.6 (V+); also elsewhere on the board
+10V: C23.1, C24.1, IC6.6 (V+), IC7.8 (V+); also elsewhere on the board
ADC_VOLTAGE: C53.2, IC15.1 (OUT), IC15.4 (IN-); also elsewhere on the board
CE: R38.2, X2.1
DAC_AUX: IC5.5 (!AUX); also elsewhere on the board
GND: C17.2, C18.2, C21.2, C22.2, C23.2, C24.2, C25.2, C42.2, C46.2, IC4.2 (GND), IC5.2 (ADDR), IC5.8 (GND), IC6.2 (V-), IC7.4 (V-), IC15.2 (V-), R25.1, R42.1; also elsewhere on the board
unnamed: IC5.6 (OUT), R23.2
unnamed: IC7.6 (IN-), IC7.7 (OUT), R24.2
unnamed: C53.1, C55.2, IC6.4 (IN-), R24.1, R25.2, R46.2
unnamed: C42.1, IC6.3 (IN+), R23.1
unnamed: C55.1, IC6.1 (OUT), R38.1
unnamed: IC5.3 (SCL), R39.2
unnamed: R42.2, X2.2, X2.4, X2.6, X2.7, X2.8, X2.9, X2.G2
unnamed: R35.2, X2.G1
unnamed: IC5.4 (SDA), R40.2
unnamed: C46.1, IC15.3 (IN+), R46.1
RE: IC7.5 (IN+), X2.3
SCL: R39.1; also elsewhere on the board
SDA: R40.1; also elsewhere on the board
VREF: C18.1, C21.1, IC4.5 (VREF), IC5.1 (REF), R35.1; also elsewhere on the board
WE: X2.5; also elsewhere on the board

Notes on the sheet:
~ 80 Hz
Notes: • Scan rate is from 1 to 100 mV/s • DAC resolution is 0.5 mV → max. 200 Hz • Target sample rate is 1 kHz
~1.6 kHz
Copyright (c) 2021 - 2023 Bonn-Rhein-Sieg University of Applied Sciences Licensed under the terms of CC BY-SA

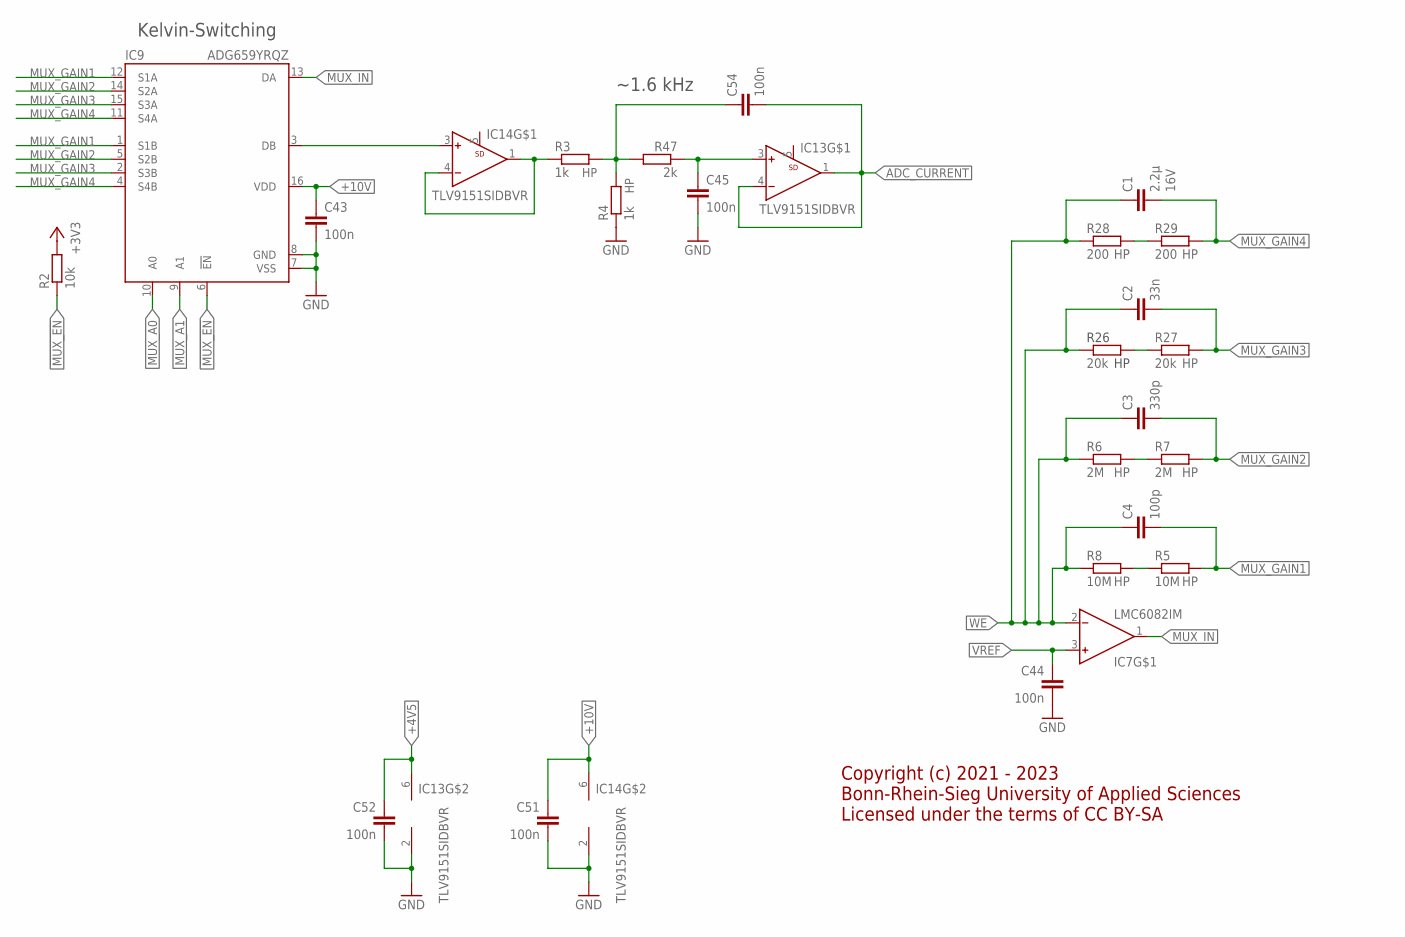
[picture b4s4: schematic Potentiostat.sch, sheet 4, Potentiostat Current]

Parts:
C1: 2.2µ; C0603; RATING 16V
C2: 33n; C0603
C3: 330p; C0603
C4: 100p; C0603
C43, C44, C45, C51, C52, C54: 100n; C0603
IC7: LMC6082IM; SOIC8
IC9: ADG659YRQZ; QSOP16
IC13, IC14: TLV9151SIDBVR; SOT23-6
R2: 10k; R0603
R3, R4: 1k; R0603
R5, R8: 10M; R0805
R6, R7: 2M; R0805
R26, R27: 20k; R0805
R28, R29: 200; R0805
R47: 2k; R0603

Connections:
!MUX_EN: IC9.6 (!EN), R2.1; also elsewhere on the board
+3V3: R2.2; also elsewhere on the board
+4V5: C52.1, IC13.6 (V+); also elsewhere on the board
+10V: C43.1, C51.1, IC9.16 (VDD), IC14.6 (V+); also elsewhere on the board
ADC_CURRENT: C54.2, IC13.1 (OUT), IC13.4 (IN-); also elsewhere on the board
GND: C43.2, C44.2, C45.2, C51.2, C52.2, IC9.7 (VSS), IC9.8 (GND), IC13.2 (V-), IC14.2 (V-), R4.1; also elsewhere on the board
MUX_A0: IC9.10 (A0); also elsewhere on the board
MUX_A1: IC9.9 (A1); also elsewhere on the board
MUX_GAIN1: C4.2, IC9.1 (S1B), IC9.12 (S1A), R5.2
MUX_GAIN2: C3.2, IC9.5 (S2B), IC9.14 (S2A), R7.2
MUX_GAIN3: C2.2, IC9.2 (S3B), IC9.15 (S3A), R27.2
MUX_GAIN4: C1.2, IC9.4 (S4B), IC9.11 (S4A), R29.2
MUX_IN: IC7.1 (OUT), IC9.13 (DA)
MUX_OUT: IC9.3 (DB), IC14.3 (IN+)
unnamed: C45.1, IC13.3 (IN+), R47.1
unnamed: R5.1, R8.2
unnamed: R6.2, R7.1
unnamed: R26.2, R27.1
unnamed: R28.2, R29.1
unnamed: IC14.1 (OUT), IC14.4 (IN-), R3.1
unnamed: C54.1, R3.2, R4.2, R47.2
VREF: C44.1, IC7.3 (IN+); also elsewhere on the board
WE: C1.1, C2.1, C3.1, C4.1, IC7.2 (IN-), R6.1, R8.1, R26.1, R28.1; also elsewhere on the board

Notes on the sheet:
Kelvin-Switching
~1.6 kHz
Copyright (c) 2021 - 2023 Bonn-Rhein-Sieg University of Applied Sciences Licensed under the terms of CC BY-SA

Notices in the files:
Firmware/ConductanceMaster/Core/Src/main.c:
© Copyright (c) 2021 STMicroelectronics.
All rights reserved.
This software component is licensed by ST under BSD 3-Clause license,
the "License"; You may not use this file except in compliance with the
License. You may obtain a copy of the License at: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
parts and their libraries:
WR-PHD: Copyright: Würth Elektronik
COPYRIGHT: Copyright (C) 2021 Ultra Librarian. All rights reserved.
